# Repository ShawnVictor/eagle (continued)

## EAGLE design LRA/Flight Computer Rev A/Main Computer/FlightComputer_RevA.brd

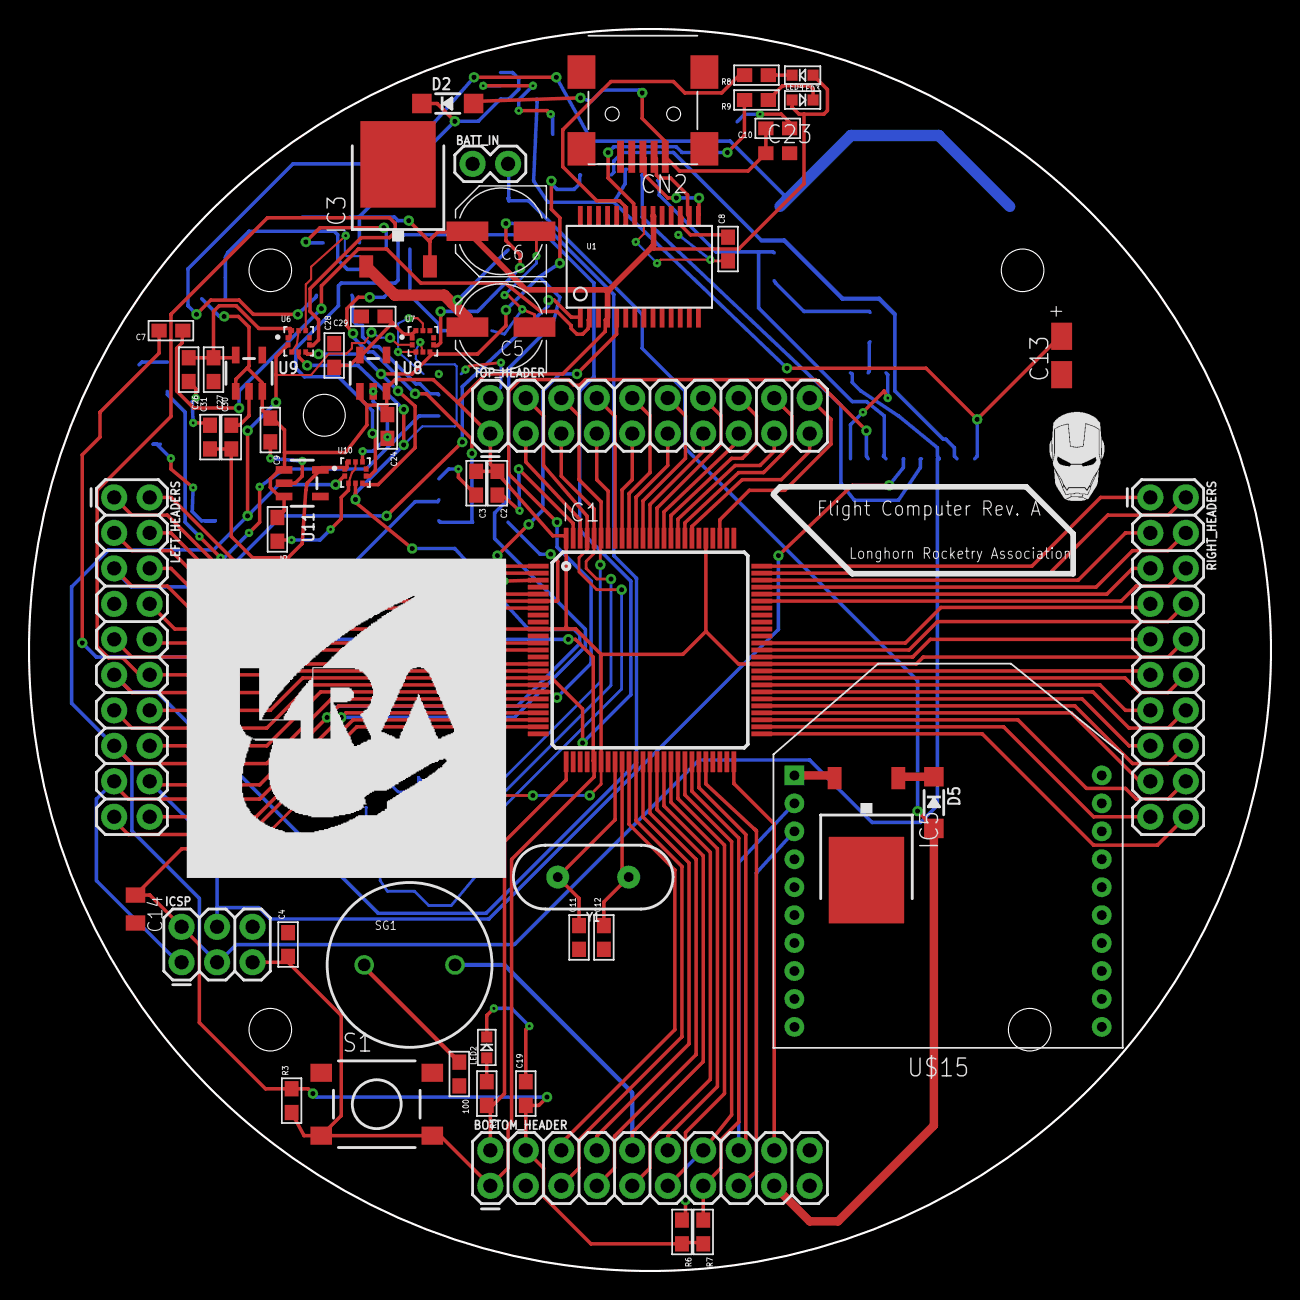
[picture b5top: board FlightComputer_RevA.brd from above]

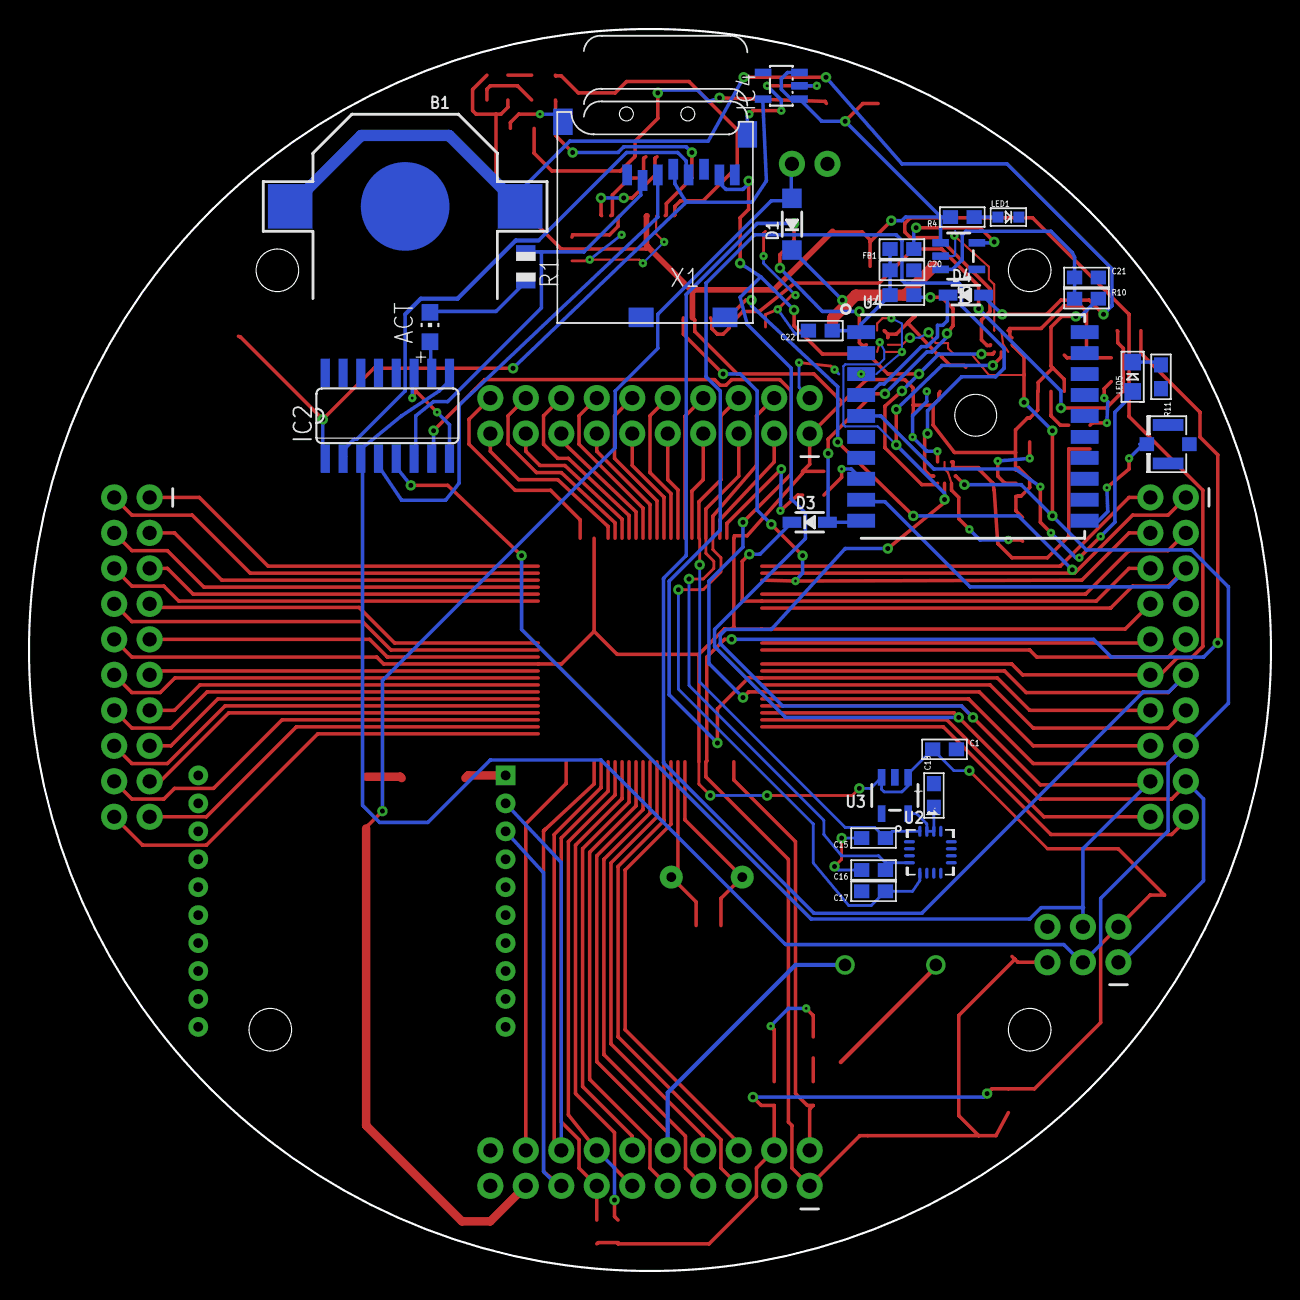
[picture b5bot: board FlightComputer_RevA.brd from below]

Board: 2 copper layers, 88.9 x 88.9 mm, 85 parts (29 on the bottom side), 108 nets.

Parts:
100: 680; 0603
ACT: RED; CHIP-LED0805
B1: CR1220
BATT_IN: 1X02
BOTTOM_HEADER: 2X10
C1, C2, C3, C7, C8, C10: 0.1uF; 0603
C4, C11, C12: 22pF; 0603
C5, C6: 47uF; PANASONIC_D
C9, C18, C19, C20, C21, C24, C25: 10µF; 0603
C13: 10uF/10V; A/3216-18R
C14: 0.1uF; C0805K
C15, C16, C17: 0.01uF; 0603
C22: 0.1µF; 0603
C23: 4.7uF; C0603
C26, C27, C28, C29, C30, C31: 100nF; 0603
CN2: USB-MINIB
D1, D2, D5: SOD-123
D3: 1N4148; SOD-323
D4: CUS520; SOD-323
FB1: 0603
IC1: ATMEGA640-16AI; TQFP100
IC2: 4050D; SO16
IC3, IC5: 7808DT; TO252
IC4: LP298XS; SOT23-5L
ICSP: FEMALE 2x3; 2X3
LED1: GREEN; CHIPLED_0603
LED2: YELLOW; CHIPLED_0603
LED3: BLUE; CHIPLED_0603
LED4: RED; CHIPLED_0603
LED5: RED; CHIPLED_0805
LEFT_HEADERS: 2X10
R1: 1K; R0805
R2, R3, R6, R7, R10: 10k; 0603
R4, R5, R11: 1k; 0603
R8, R9: 680; 0603
RIGHT_HEADERS: 2X10
S1: DTSM-6
SG1: BUZZERPTH; BUZZER-12MM
TOP_HEADER: 2X10
U1: SSOP28DB
U2: ADXL377; LFCSP16_LQ
U3, U8, U9, U11: RT9193; SOT23-5
U4: FGPMMOPA6H
U5: MIC5225-3.3; SOT23-5
U6, U7, U10: BMP388; PQFN50P200X200X80-10N
U$15: XBEE
U$55: U.FL
X1: MICROSD
Y1: 16MHz; HC49US

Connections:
3.3V: C8.2, U1.17
5.0V: BOTTOM_HEADER.4, C1.1, C2.1, C3.1, C6.+, C9.1, C14.1, C19.1, C24.1, C25.1, D2.C, IC1.10, IC1.31, IC1.61, IC1.80, IC1.100, IC3.2, IC4.1, IC4.3, ICSP.2, LED3.A, LED4.A, LEFT_HEADERS.8, R3.2, R4.2, R6.2, R7.2, R10.2, RIGHT_HEADERS.10, TOP_HEADER.1, U1.4, U1.20, U3.1, U3.3, U5.1, U8.1, U8.3, U9.1, U9.3, U11.1, U11.3
+3V3: C13.+, IC2.1, IC4.5, X1.4
ADC0: C17.1, IC1.97, TOP_HEADER.4, U2.5
ADC1: C16.1, IC1.96, TOP_HEADER.5, U2.4
ADC2: C15.1, IC1.95, TOP_HEADER.6, U2.16
ADC3: IC1.94, TOP_HEADER.7
ADC4: IC1.93, TOP_HEADER.8
ADC5: IC1.92, TOP_HEADER.9
ADC6: IC1.91, TOP_HEADER.10
ADC7: IC1.90, TOP_HEADER.11
ADC8: IC1.89, TOP_HEADER.12
ADC9: IC1.88, TOP_HEADER.13
ADC10: IC1.87, TOP_HEADER.14
ADC11: IC1.86, TOP_HEADER.15
ADC12: IC1.85, TOP_HEADER.16
ADC13: IC1.84, TOP_HEADER.17
ADC14: IC1.83, TOP_HEADER.18
ADC15: IC1.82, TOP_HEADER.19
AREF: IC1.98, TOP_HEADER.3
BATT_IN: BATT_IN.2, BOTTOM_HEADER.17, D1.A, D5.A
D0_RX0: IC1.2, LEFT_HEADERS.1, U1.1
D1_TX0: IC1.3, LEFT_HEADERS.4, U1.5
D2: D3.C, IC1.6, LEFT_HEADERS.6
D3: IC1.7, LEFT_HEADERS.5, U4.P$9
D4: IC1.1, LEFT_HEADERS.2
D5: IC1.5, LEFT_HEADERS.3
D6: IC1.15, LEFT_HEADERS.12, U6.6
D7: IC1.16, LEFT_HEADERS.11, U7.6
D8: IC1.17, LEFT_HEADERS.14, U10.6
D9: IC1.18, LEFT_HEADERS.13
D10: IC1.23, LEFT_HEADERS.20
D11: IC1.24, LEFT_HEADERS.19
D13: BOTTOM_HEADER.2, IC1.26, R5.2
D14_TX3: IC1.64, RIGHT_HEADERS.7
D15_RX3: IC1.63, RIGHT_HEADERS.8
D16_TX2: IC1.13, LEFT_HEADERS.9
D17_RX2: IC1.12, LEFT_HEADERS.10
D18_TX1: BOTTOM_HEADER.15, IC1.46, U$15.3
D19_RX1: BOTTOM_HEADER.16, IC1.45, U$15.2
D20_SDA: BOTTOM_HEADER.13, IC1.44, R7.1
D21_SCL: BOTTOM_HEADER.14, IC1.43, R6.1
D22: IC1.78, TOP_HEADER.20
D25: IC1.75, RIGHT_HEADERS.1
D26: IC1.74, RIGHT_HEADERS.2
D27: IC1.73, RIGHT_HEADERS.3
D28: IC1.72, RIGHT_HEADERS.4
D29: IC1.71, RIGHT_HEADERS.5
D30: IC1.60, RIGHT_HEADERS.11
D31: IC1.59, RIGHT_HEADERS.12
D32: IC1.58, RIGHT_HEADERS.13
D33: IC1.57, RIGHT_HEADERS.14
D34: IC1.56, RIGHT_HEADERS.15
D35: IC1.55, RIGHT_HEADERS.16
D36: IC1.54, RIGHT_HEADERS.17
D37: IC1.53, RIGHT_HEADERS.18
D38: BOTTOM_HEADER.18, IC1.50
D39: IC1.70, RIGHT_HEADERS.6
D40: IC1.52, RIGHT_HEADERS.19
D41: IC1.51, RIGHT_HEADERS.20
D42: BOTTOM_HEADER.11, IC1.42
D43: BOTTOM_HEADER.12, IC1.41
D44: BOTTOM_HEADER.9, IC1.40
D45: BOTTOM_HEADER.10, IC1.39, SG1.+
D46: BOTTOM_HEADER.7, IC1.38
D47: BOTTOM_HEADER.8, IC1.37
D48: BOTTOM_HEADER.5, IC1.36
D49: BOTTOM_HEADER.6, IC1.35
D50_MISO: IC1.22, ICSP.1, LEFT_HEADERS.17, U6.5, U7.5, U10.5, X1.7
D51_MOSI: IC1.21, IC2.5, ICSP.4, LEFT_HEADERS.18, U6.4, U7.4, U10.4
D52_SCK: IC1.20, IC2.3, IC2.9, ICSP.3, LEFT_HEADERS.15, U6.2, U7.2, U10.2
D53_SS: IC1.19, IC2.7, LEFT_HEADERS.16
FIX: LED5.A, U4.P$5
GND: 100.2, B1.-, BATT_IN.1, BOTTOM_HEADER.3, BOTTOM_HEADER.19, BOTTOM_HEADER.20, C1.2, C2.2, C3.2, C4.2, C5.-, C6.-, C8.1, C9.2, C10.1, C11.1, C12.1, C13.-, C14.2, C15.2, C16.2, C17.2, C18.2, C19.2, C20.2, C21.2, C22.2, C23.2, C24.2, C25.2, C26.2, C27.2, C28.2, C29.2, C30.2, C31.2, CN2.GND, IC1.11, IC1.32, IC1.62, IC1.81, IC1.99, IC2.8, IC2.11, IC2.14, IC3.3, IC4.2, IC5.3, ICSP.6, LED1.C, LED2.C, LEFT_HEADERS.7, R11.2, RIGHT_HEADERS.9, S1.1, S1.2, TOP_HEADER.2, U1.7, U1.18, U1.21, U1.25, U2.1, U2.3, U2.6, U2.7, U3.2, U4.P$3, U4.P$8, U4.P$12, U4.P$19, U5.2, U6.3, U6.8, U6.9, U7.3, U7.8, U7.9, U8.2, U9.2, U10.3, U10.8, U10.9, U11.2, U$15.10, U$55.P$1, U$55.P$2, X1.6, X1.MT1, X1.MT2
unnamed: ACT.A, IC2.10
unnamed: D5.C, IC5.1
unnamed: CN2.D+, U1.15
unnamed: CN2.D-, U1.16
unnamed: LED1.A, R4.1
unnamed: LED2.A, R5.1
unnamed: LED3.C, R8.1
unnamed: R9.2, U1.22
unnamed: R8.2, U1.23
unnamed: LED4.C, R9.1
unnamed: IC2.2, X1.5
unnamed: C7.1, U1.2
unnamed: IC2.6, R1.1, X1.2
unnamed: ACT.C, R1.2
unnamed: IC2.4, X1.3
unnamed: U4.P$11, U$55.P$3
unnamed: C18.1, U2.14, U2.15, U3.5
unnamed: C21.1, R10.1, U5.3
unnamed: D3.A, R2.1, U4.P$10
unnamed: B1.+$1, B1.+$2, D4.A
unnamed: C20.1, C22.1, FB1.2, R2.2, U4.P$1
unnamed: 100.1, SG1.-
unnamed: LED5.C, R11.1
OUT: FB1.1, U5.5
OUT1: C26.1, C27.1, U6.1, U6.10, U9.5
OUT2: C28.1, C29.1, U7.1, U7.10, U8.5
OUT3: C30.1, C31.1, U10.1, U10.10, U11.5
RESET: BOTTOM_HEADER.1, C4.1, C7.2, IC1.30, ICSP.5, R3.1, S1.3, S1.4
VBACKUP: D4.C, U4.P$4
VCC: IC5.2, U$15.1
VIN: C5.+, D1.C, IC3.1
VUSB: C10.2, C23.1, CN2.VBUS, D2.A
XTAL1: C12.2, IC1.34, Y1.1
XTAL2: C11.2, IC1.33, Y1.2
